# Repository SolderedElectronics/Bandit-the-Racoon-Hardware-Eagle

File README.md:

# Bandit the Racoon hardware (Eagle Files)
## Image

[Bandit the Racoon board(101413)][board]

## Description and details
Bandit the Racoon is a cool looking board made for programming education which eliminates all need to work with hardware - everything is already connected and ready to use on the board. It can be programmed with block programming which is best for programming logic learning and with Arduino programming using Arduino library or using classic Arduino programming.
Onboard, there are many different sensors and actuators which can be used directly. All you need to do is connect the USB cable to the PC and you are ready to program and play! It supports battery power as well, there is battery charger onboard, so your projects can be portable.

###Specs:
- Temperature sensor
- Light sensor 
- Pushbutton
- Switch
- Potentiometer
- General input pins
- 12 RGB LED diodes arranged into a circle
- Buzzer
- General output pins
- I2C connector
- Atmega328 microcontroller
- CP2102 USB to UART bridge
- Lithium charger onboard

###Exact pins connections
If you wish to make your own Arduino code, here is list of all Arduino sensors and actuators and pins to which are they connected to. 

## Repository content
This repo contains Cadsoft Eagle .sch and .brd files for BTR board. It also contains schematic in .pdf created from .sch Eagle file. 
Files have been arranged into folders for navigating between different versions of board. 
Tip: layer 200 shows top silkscreen and layer 208 should be bottom silkscreen. tParts and bParts is not used.

## Docs
- [BTR product page][board]
- [BTR Arduino library][library]

## Board versions
- v1.0 - inital version

## License info
This product is open-source. Yay!
For any tech questions, contact us at techsupport@e-radionica.com
If you find an Issue, please open one at GitHub. If you can improve our product, fork it!

e-r.io Team.

[board]: https://e-radionica.com/en/bandit-the-raccoon-btr.html
[library]: https://github.com/e-radionicacom/Bandit-the-Racoon-Arduino-library

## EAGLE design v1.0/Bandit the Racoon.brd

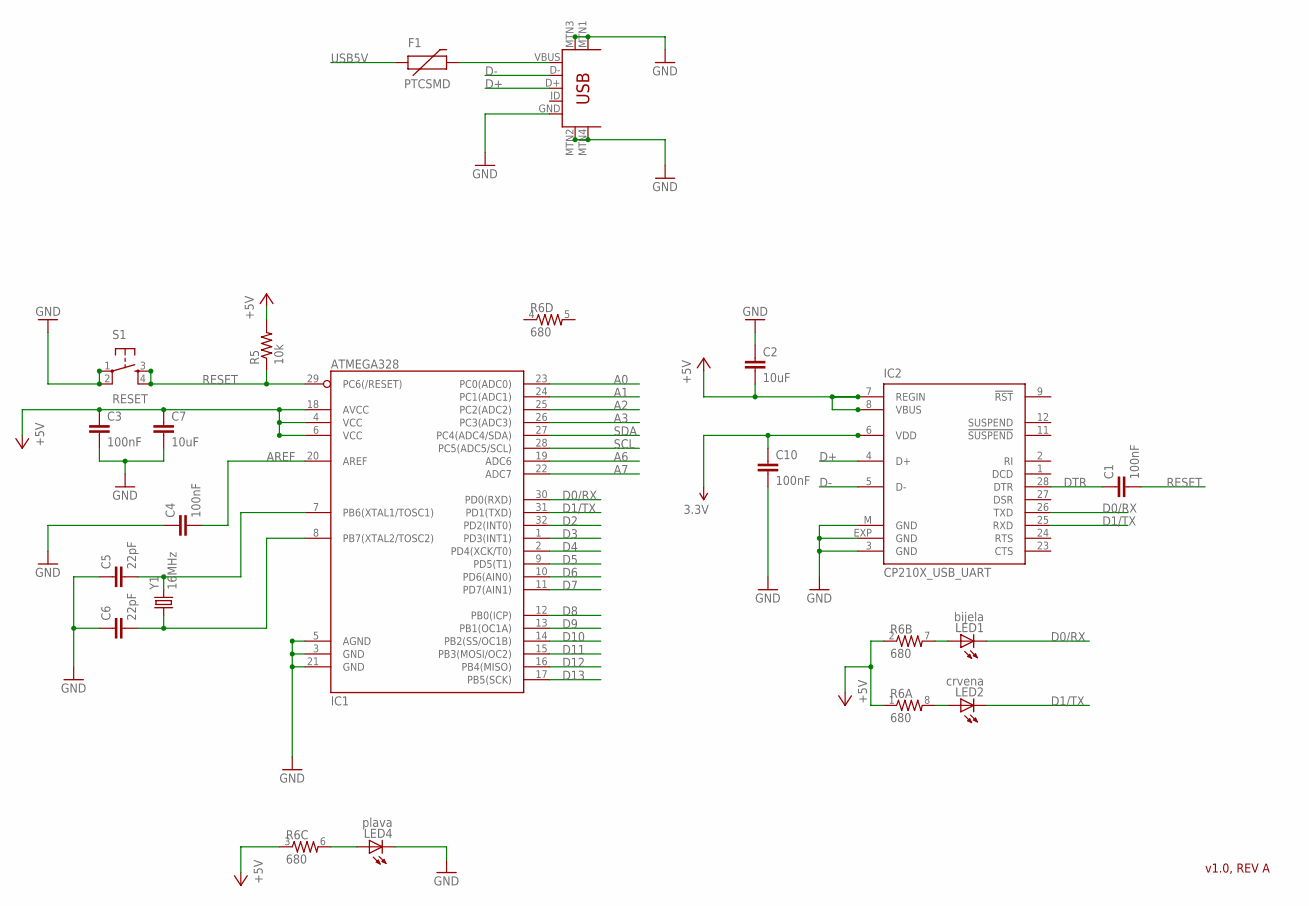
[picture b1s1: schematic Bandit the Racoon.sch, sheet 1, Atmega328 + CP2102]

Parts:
C1, C3, C4, C10: 100nF; 0603-CAP
C2, C7: 10uF; C3216
C5, C6: 22pF; 0603-CAP
F1: PTCSMD; PTC-1206
IC1: ATMEGA328; TQFP32-08
IC2: CP210X_USB_UART; MLP28
LED1: bijela; CHIP-LED0805
LED2: crvena; CHIP-LED0805
LED4: plava; CHIP-LED0805
R5: 10k; 0603-RES
R6: 680; 0603-ARV
S1: RESET; TACTILE_SWITCH_SMD
U1: USB-MINIB
Y1: 16MHz; CRYSTAL-SMD-5X3

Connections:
3.3V: C10.1, IC2.6 (VDD); also elsewhere on the board
+5V: C2.2, C3.1, C7.1, IC1.4 (VCC), IC1.6 (VCC), IC1.18 (AVCC), IC2.7 (REGIN), IC2.8 (VBUS), R5.2, R6.1, R6.2 (1), R6.3 (1); also elsewhere on the board
A0: IC1.23 (PC0(ADC0)); also elsewhere on the board
A1: IC1.24 (PC1(ADC1)); also elsewhere on the board
A2: IC1.25 (PC2(ADC2)); also elsewhere on the board
A3: IC1.26 (PC3(ADC3)); also elsewhere on the board
A6: IC1.19 (ADC6)
A7: IC1.22 (ADC7)
AREF: C4.2, IC1.20 (AREF)
CRYSTAL1: C5.2, IC1.7 (PB6(XTAL1/TOSC1)), Y1.3 (2)
CRYSTAL2: C6.2, IC1.8 (PB7(XTAL2/TOSC2)), Y1.1
D0/RX: IC1.30 (PD0(RXD)), IC2.26 (TXD), LED1.C; also elsewhere on the board
D1/TX: IC1.31 (PD1(TXD)), IC2.25 (RXD), LED2.C; also elsewhere on the board
D2: IC1.32 (PD2(INT0)); also elsewhere on the board
D3: IC1.1 (PD3(INT1)); also elsewhere on the board
D4: IC1.2 (PD4(XCK/T0)); also elsewhere on the board
D5: IC1.9 (PD5(T1)); also elsewhere on the board
D6: IC1.10 (PD6(AIN0))
D7: IC1.11 (PD7(AIN1))
D8: IC1.12 (PB0(ICP))
D9: IC1.13 (PB1(OC1A)); also elsewhere on the board
D10: IC1.14 (PB2(SS/OC1B))
D11: IC1.15 (PB3(MOSI/OC2))
D12: IC1.16 (PB4(MISO))
D13: IC1.17 (PB5(SCK))
D+: IC2.4 (D+), U1.D+
D-: IC2.5 (D-), U1.D-
DTR: C1.1, IC2.28 (DTR); also elsewhere on the board
GND: C2.1, C3.2, C4.1, C5.1, C6.1, C7.2, C10.2, IC1.3 (GND), IC1.5 (AGND), IC1.21 (GND), IC2.3 (GND), IC2.EXP (GND), IC2.M (GND), LED4.C, S1.1, S1.2, U1.GND, U1.MTN1 (MTN2), U1.MTN2 (MTN3), U1.MTN3 (MTN1), U1.MTN4; also elsewhere on the board
unnamed: LED1.A, R6.7 (2)
unnamed: LED2.A, R6.8 (2)
unnamed: F1.2, U1.VBUS
PLV_LED: LED4.A, R6.6 (2)
RESET: C1.2, IC1.29 (PC6(/RESET)), R5.1, S1.3, S1.4
SCL: IC1.28 (PC5(ADC5/SCL)); also elsewhere on the board
SDA: IC1.27 (PC4(ADC4/SDA)); also elsewhere on the board
USB5V: F1.1; also elsewhere on the board

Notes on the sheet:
v1.0, REV A

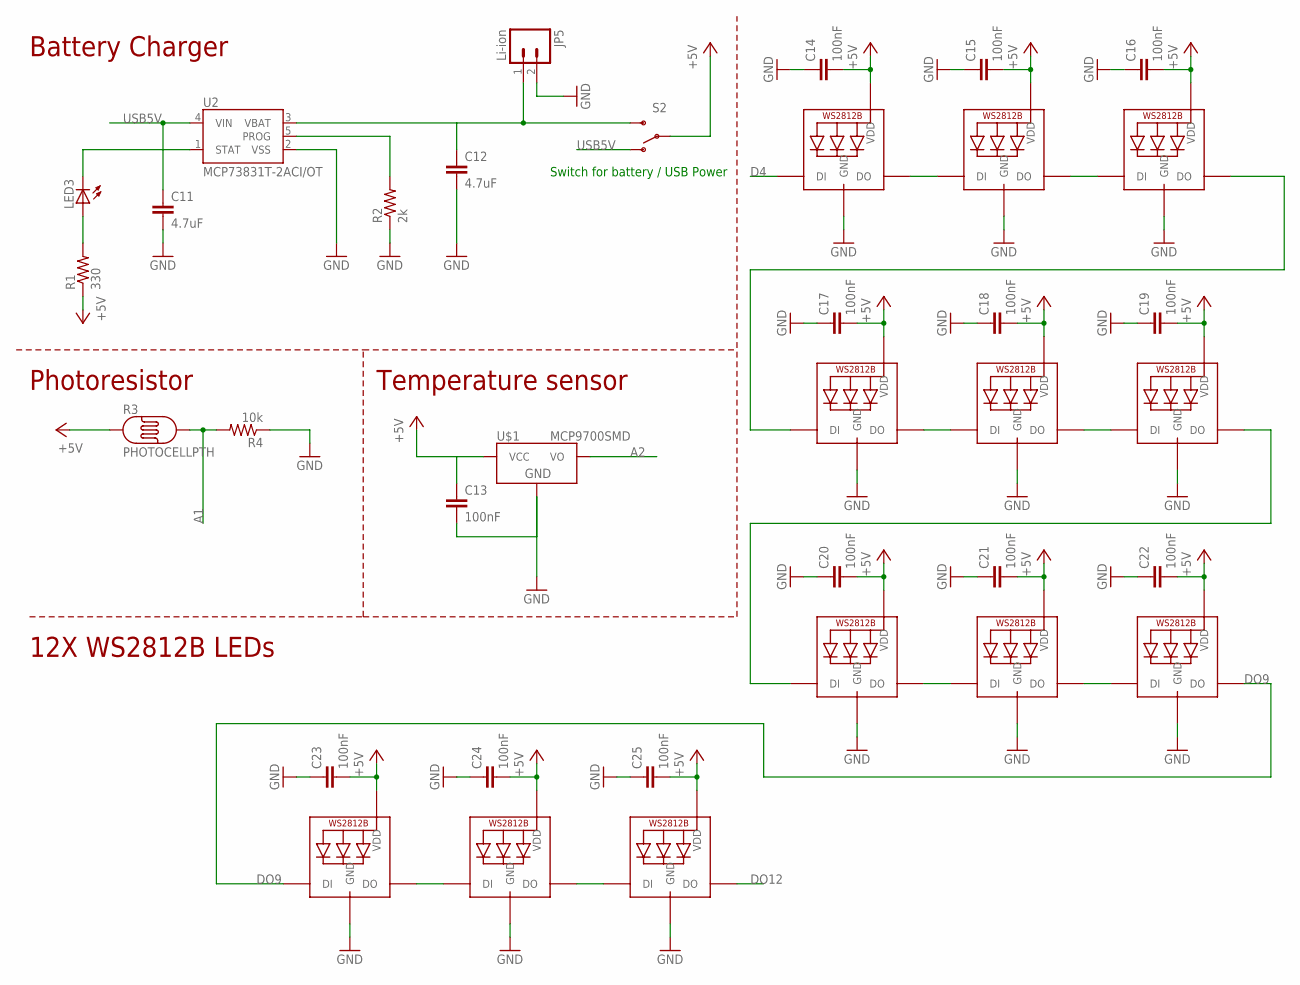
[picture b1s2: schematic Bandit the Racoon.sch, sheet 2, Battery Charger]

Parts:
C11, C12: 4.7uF; 0805
C13, C14, C15, C16, C17, C18, C19, C20, C21, C22, C23, C24, C25: 100nF; 0603-CAP
JP5: Li-ion; JST-2-PTH
LED3: LEDCHIPLED_0805; CHIPLED_0805
LED5, LED6, LED7, LED8, LED9, LED10, LED11, LED12, LED13, LED14, LED15, LED16: WS2812B5050; WS2812B
R1: 330; 0603-RES
R2: 2k; 0603-RES
R3: PHOTOCELLPTH; PHOTOCELL
R4: 10k; 0603-RES
S2: SWITCH-SPST-SMD-A
U2: MCP73831T-2ACI/OT; SOT23-5
U$1: MCP9700SMD; SOT23-3

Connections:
+5V: C13.1, C14.2, C15.2, C16.2, C17.2, C18.2, C19.2, C20.2, C21.2, C22.2, C23.2, C24.2, C25.2, LED5.1-VDD (VDD), LED6.1-VDD (VDD), LED7.1-VDD (VDD), LED8.1-VDD (VDD), LED9.1-VDD (VDD), LED10.1-VDD (VDD), LED11.1-VDD (VDD), LED12.1-VDD (VDD), LED13.1-VDD (VDD), LED14.1-VDD (VDD), LED15.1-VDD (VDD), LED16.1-VDD (VDD), R1.1, R3.1, S2.2, U$1.1 (VCC); also elsewhere on the board
A1: R3.2, R4.2; also elsewhere on the board
A2: U$1.2 (VO); also elsewhere on the board
D4: LED5.4-DIN (DI); also elsewhere on the board
DO1: LED5.2-DOUT (DO), LED6.4-DIN (DI)
DO2: LED6.2-DOUT (DO), LED7.4-DIN (DI)
DO3: LED7.2-DOUT (DO), LED8.4-DIN (DI)
DO4: LED8.2-DOUT (DO), LED9.4-DIN (DI)
DO5: LED9.2-DOUT (DO), LED10.4-DIN (DI)
DO6: LED10.2-DOUT (DO), LED11.4-DIN (DI)
DO7: LED11.2-DOUT (DO), LED12.4-DIN (DI)
DO8: LED12.2-DOUT (DO), LED13.4-DIN (DI)
DO9: LED13.2-DOUT (DO), LED14.4-DIN (DI)
DO10: LED14.2-DOUT (DO), LED15.4-DIN (DI)
DO11: LED15.2-DOUT (DO), LED16.4-DIN (DI)
DO12: LED16.2-DOUT (DO)
GND: C11.2, C12.2, C13.2, C14.1, C15.1, C16.1, C17.1, C18.1, C19.1, C20.1, C21.1, C22.1, C23.1, C24.1, C25.1, JP5.2, LED5.3-GND (GND), LED6.3-GND (GND), LED7.3-GND (GND), LED8.3-GND (GND), LED9.3-GND (GND), LED10.3-GND (GND), LED11.3-GND (GND), LED12.3-GND (GND), LED13.3-GND (GND), LED14.3-GND (GND), LED15.3-GND (GND), LED16.3-GND (GND), R2.1, R4.1, U2.2 (VSS), U$1.3 (GND); also elsewhere on the board
unnamed: LED3.C, U2.1 (STAT)
unnamed: LED3.A, R1.2
unnamed: C12.1, JP5.1, S2.3 (S), U2.3 (VBAT)
unnamed: R2.2, U2.5 (PROG)
USB5V: C11.1, S2.1 (O), U2.4 (VIN); also elsewhere on the board

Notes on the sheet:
Switch for battery / USB Power
Battery Charger
Photoresistor
Temperature sensor
12X WS2812B LEDs

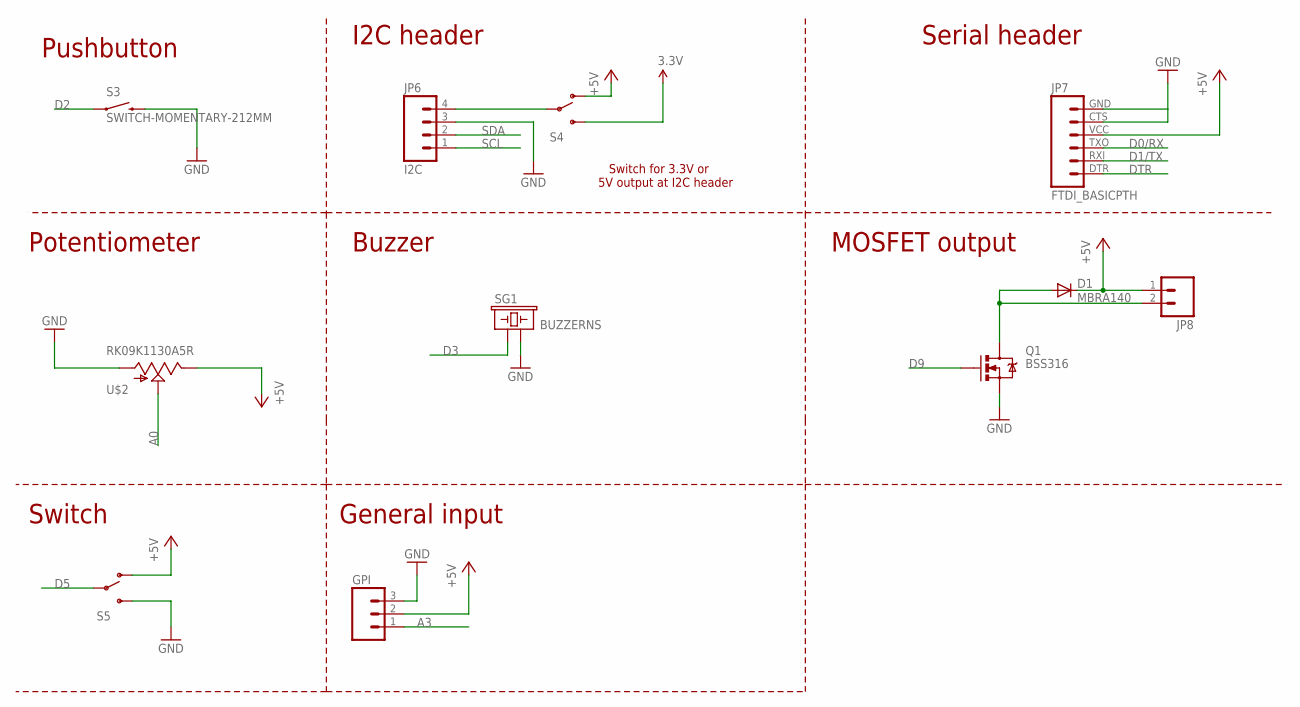
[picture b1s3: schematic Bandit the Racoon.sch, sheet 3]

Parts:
D1: MBRA140; SMA-DIODE
GPI: M03LONGPADS; 1X03_LONGPADS
JP6: I2C; 1X04_LONGPADS
JP7: FTDI_BASICPTH; FTDI_BASIC
JP8: M02PTH; 1X02
Q1: BSS316; SOT23-3
S3: SWITCH-MOMENTARY-212MM; TACTILE-PTH-12MM
S4: SWITCH-SPST-SMD-A
S5: SWITCH-SPSTKIT; SWITCH-SPDT_KIT
SG1: BUZZERNS; BUZZER-12MM-NS
U$2: RK09K1130A5R; ALPS_POT

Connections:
3.3V: S4.3 (S); also elsewhere on the board
+5V: D1.C, GPI.2, JP7.VCC (4), JP8.1, S4.1 (O), S5.1 (O), U$2.P$1 (E); also elsewhere on the board
A0: U$2.P$2 (S); also elsewhere on the board
A3: GPI.1; also elsewhere on the board
D0/RX: JP7.TXO (3); also elsewhere on the board
D1/TX: JP7.RXI (2); also elsewhere on the board
D2: S3.1; also elsewhere on the board
D3: SG1.+ (1); also elsewhere on the board
D5: S5.2; also elsewhere on the board
D9: Q1.1 (G); also elsewhere on the board
DTR: JP7.DTR (1); also elsewhere on the board
GND: GPI.3, JP6.3, JP7.CTS (5), JP7.GND (6), Q1.2 (S), S3.3 (2), S5.3 (S), SG1.- (2), U$2.P$3 (A); also elsewhere on the board
unnamed: JP6.4, S4.2
unnamed: D1.A, JP8.2, Q1.3 (D)
SCL: JP6.1; also elsewhere on the board
SDA: JP6.2; also elsewhere on the board

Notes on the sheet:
Pushbutton
Potentiometer
Buzzer
MOSFET output
Serial header
I2C header
Switch for 3.3V or 5V output at I2C header
Switch
General input

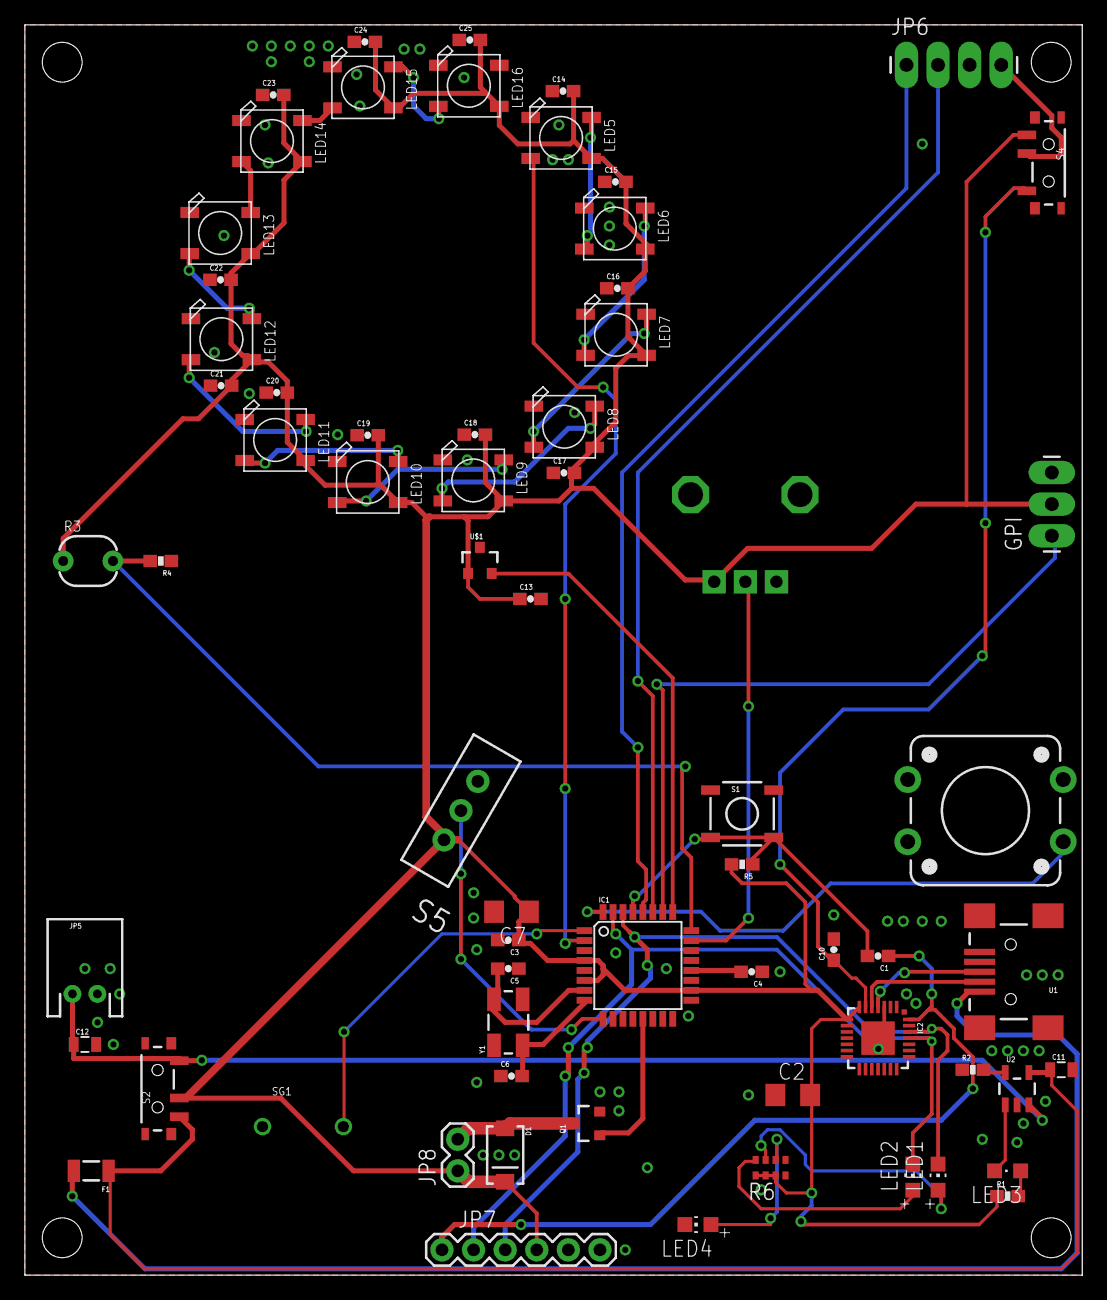
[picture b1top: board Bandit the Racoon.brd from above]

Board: 2 copper layers, 85.0 x 100.5 mm, 72 parts (0 on the bottom side), 45 nets.

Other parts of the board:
U$3: BANDIT_THE_RACOON
U$4: E-RADIONICA.COM_MADE_IN_BACK!
U$5: OSH3MM
U$6: E-RADIONICA.COM_MADE_IN
U$7: NOVI_LOGO-4MM
U$8: LUDI_LOGO_BACK

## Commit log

2017-05-28 Init

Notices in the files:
parts and their libraries:
SparkFun: Licensing: CC v3.0 Share-Alike You are welcome to use this library for commercial purposes.
SparkFun-DigitalIC: Licensing: Creative Commons ShareAlike 4.0 International - https://creativecommons.org/licenses/by-sa/4.0
